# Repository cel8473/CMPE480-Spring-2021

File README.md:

# CMPE480-Spring-2021
 Interface & Digital Electronics at RIT during Spring 2021
 
Lab 1: Intro to K64F GPIO and Keil MicroVision

Lab 2: UART Driver

Lab 3: Characterization of OPB745

Lab 4: UART Over Bluetooth

Lab 5: K64 Timers, Interrupts, and Analog-To-Digital Converter

Lab 6: Motor Control

Lab 7: Filter Design and Simulation

Lab 8: Heartrate Monitor

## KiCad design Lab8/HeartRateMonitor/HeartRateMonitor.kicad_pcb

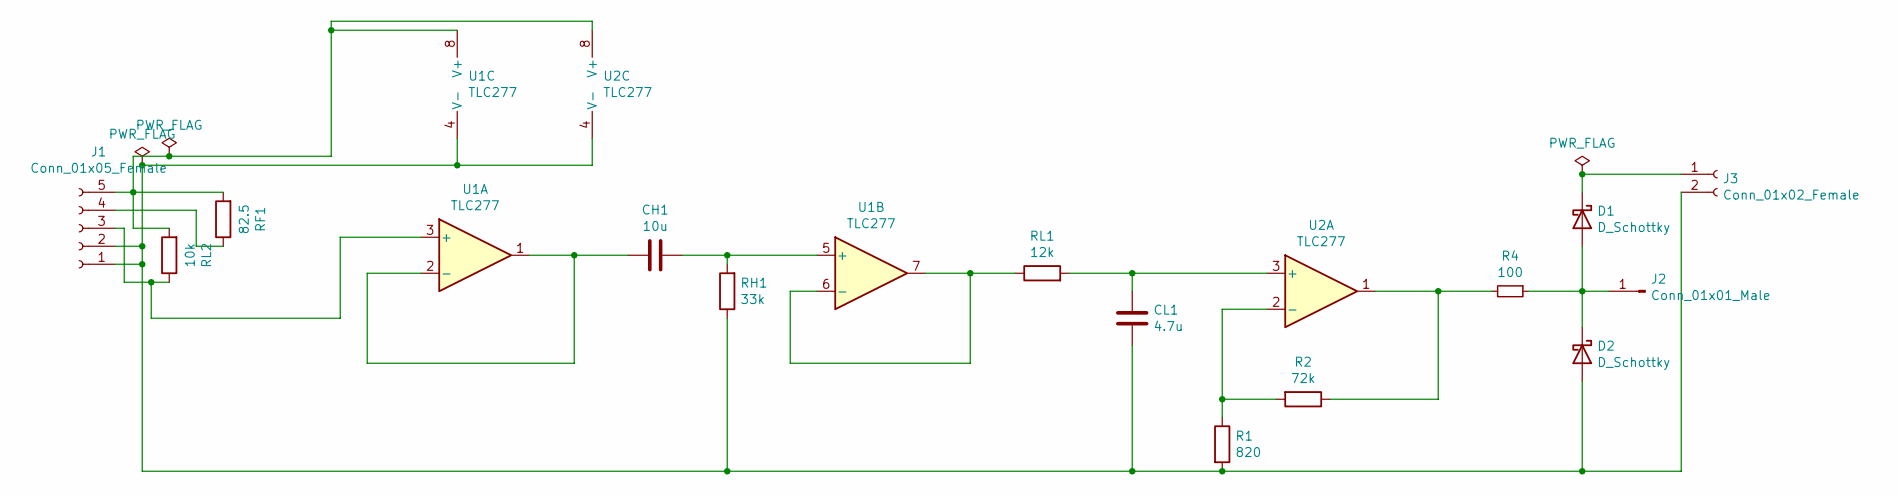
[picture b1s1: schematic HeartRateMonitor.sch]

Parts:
CH1: 10u; CP_Axial_L10.0mm_D4.5mm_P15.00mm_Horizontal
CL1: 4.7u; CP_Axial_L10.0mm_D4.5mm_P15.00mm_Horizontal
D1, D2: D_Schottky; D_A-405_P2.54mm_Vertical_KathodeUp
J1: Conn_01x05_Female; PinSocket_1x05_P2.54mm_Vertical
J2: Conn_01x01_Male; PinHeader_1x01_P2.54mm_Vertical
J3: Conn_01x02_Female; PinSocket_1x02_P2.54mm_Vertical
R1: 820; R_Axial_DIN0204_L3.6mm_D1.6mm_P2.54mm_Vertical
R2: 72k; R_Axial_DIN0204_L3.6mm_D1.6mm_P2.54mm_Vertical
R4: 100; R_Axial_DIN0204_L3.6mm_D1.6mm_P2.54mm_Vertical
RF1: 82.5; R_Axial_DIN0204_L3.6mm_D1.6mm_P2.54mm_Vertical
RH1: 33k; R_Axial_DIN0204_L3.6mm_D1.6mm_P2.54mm_Vertical
RL1: 12k; R_Axial_DIN0204_L3.6mm_D1.6mm_P2.54mm_Vertical
RL2: 10k; R_Axial_DIN0204_L3.6mm_D1.6mm_P2.54mm_Vertical
U1, U2: TLC277; DIP794W45P254L959H508Q8

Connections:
unnamed: CH1.1, RH1.2, U1.5 (+)
unnamed: CH1.2, U1.1, U1.2 (-)
unnamed: CL1.1, D2.2 (A), J1.1, J1.2, J3.2, R1.2, RH1.1, U1.4 (V-), U2.4 (V-)
unnamed: CL1.2, RL1.2, U2.3 (+)
unnamed: D1.1 (K), J3.1
unnamed: D1.2 (A), D2.1 (K), J2.1, R4.1
unnamed: J1.3, RL2.1, U1.3 (+)
unnamed: J1.4, RF1.1
unnamed: J1.5, RF1.2, RL2.2, U1.8 (V+), U2.8 (V+)
unnamed: R1.1, R2.2, U2.2 (-)
unnamed: R2.1, R4.2, U2.1
unnamed: RL1.1, U1.6 (-), U1.7

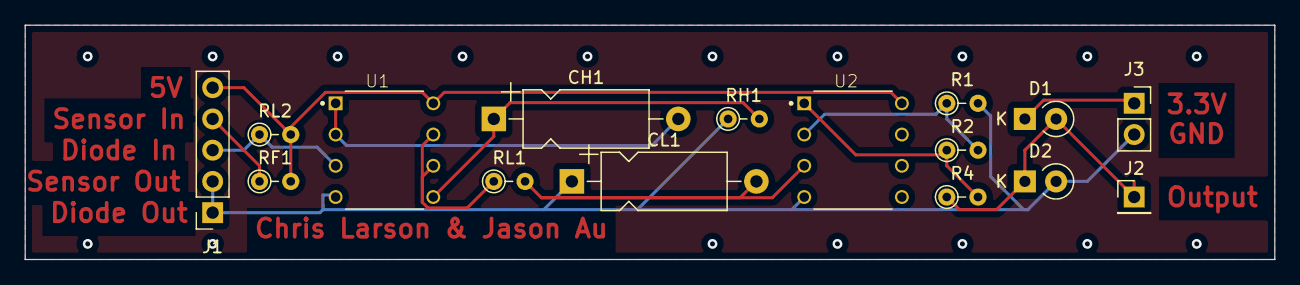
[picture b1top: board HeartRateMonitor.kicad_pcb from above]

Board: 2 copper layers, 101.6 x 19.1 mm, 16 parts (0 on the bottom side), 12 nets.

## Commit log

2021-03-12 Adding Lab 6
    20% Duty Cycle at 10kHZ
    DC Motor Functionality
    Stepper Motor Functionality- Partial
2021-03-15 Adding Lab 6 Multimotor
    This is the part of the lab where we are running multiple motors at one time.
2021-03-15 Adding #if and changing to active high
    The motor is active high and we only want to run part 3 of the lab to run the stepper motor.
2021-04-08 Adding the project
2021-04-08 Files
2021-04-08 Adding
2021-04-08 Function clean up
2021-04-08 Checkpoint #2 :)
2021-04-09 Task list
2021-04-17 Added PID
2021-04-17 Committing module changes
2021-04-21 This works and can be slowed down to 65 for the race if need be
2021-04-21 I forgot the .h files
2021-04-26 Medium speed
2021-04-28 Fixed bluetooth and faster mode yet.
2021-05-01 Code that works currently
2021-05-12 IEEE Paper for the NXP Cup Car
2021-05-13 Adding Lab 7 and Lab 8 and any last updates to NXP Cup Car
2021-05-13 Updating Read Me with the lab topics
